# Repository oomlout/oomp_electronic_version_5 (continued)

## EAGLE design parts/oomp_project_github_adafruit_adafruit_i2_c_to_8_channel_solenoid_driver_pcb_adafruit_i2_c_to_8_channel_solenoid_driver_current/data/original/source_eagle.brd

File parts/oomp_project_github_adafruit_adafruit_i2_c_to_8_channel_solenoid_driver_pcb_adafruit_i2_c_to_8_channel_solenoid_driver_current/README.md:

# Project adafruit/Adafruit-I2C-to-8-Channel-Solenoid-Driver-PCB Adafruit I2 C to 8 Channel Solenoid Driver current

[View the project on GitHub](https://github.com/adafruit/Adafruit-I2C-to-8-Channel-Solenoid-Driver-PCB/blob/main/Adafruit%20I2C%20to%208%20Channel%20Solenoid%20Driver.brd)

[Open the interactive board explorer (GitHub Pages)](https://oomlout.github.io/oomp_electronic_version_5/parts/oomp_project_github_adafruit_adafruit_i2_c_to_8_channel_solenoid_driver_pcb_adafruit_i2_c_to_8_channel_solenoid_driver_current/board_explorer.html)

[Browse this project category](../../navigation/oomp/project/github/adafruit/adafruit_i2_c_to_8_channel_solenoid_driver_pcb/adafruit_i2_c_to_8_channel_solenoid_driver/README.md)

Project adafruit/Adafruit-I2C-to-8-Channel-Solenoid-Driver-PCB Adafruit I2 C to 8 Channel Solenoid Driver current is a KiCad project containing 195 extracted component records. The catalogue matcher linked 50 physical placements to OOMP parts.

## Project snapshot

| Item | Count |
| --- | ---: |
| Components | 195 |
| PCB footprints | 135 |
| Mounting and locating holes | 4 |
| Matched OOMP mounting-hole items | 4 |
| Schematic symbols | 137 |
| Matched OOMP components | 50 |
| Unmatched physical components | 72 |
| Front-side placements | 94 |
| Back-side placements | 24 |
| Project version | `current` |
| Git ref | `main` |

## Board

[Original KiCad files](https://github.com/oomlout/oomp_electronic_version_5/tree/main/parts/oomp_project_github_adafruit_adafruit_i2_c_to_8_channel_solenoid_driver_pcb_adafruit_i2_c_to_8_channel_solenoid_driver_current/data/original) · [OOMP KiCad design and local libraries](https://github.com/oomlout/oomp_electronic_version_5/tree/main/parts/oomp_project_github_adafruit_adafruit_i2_c_to_8_channel_solenoid_driver_pcb_adafruit_i2_c_to_8_channel_solenoid_driver_current/data/oomp_design) · [Conversion / skipped-item report](https://github.com/oomlout/oomp_electronic_version_5/blob/main/parts/oomp_project_github_adafruit_adafruit_i2_c_to_8_channel_solenoid_driver_pcb_adafruit_i2_c_to_8_channel_solenoid_driver_current/data/oomp_design/conversion_report.yaml)

The OOMP design is a separate copy. Only symbols and footprints verified against unchanged installed KiCad masters are replaced; custom and modified items are retained.

- Approximate size: **50.8 mm × 27.94 mm**
- Outline source: `KiCad Edge.Cuts`
- Placement drawing: [view `board.svg`](https://github.com/oomlout/oomp_electronic_version_5/blob/main/parts/oomp_project_github_adafruit_adafruit_i2_c_to_8_channel_solenoid_driver_pcb_adafruit_i2_c_to_8_channel_solenoid_driver_current/data/generated_data/src/board.svg)
- PNG placement drawing: [view `board.png`](https://github.com/oomlout/oomp_electronic_version_5/blob/main/parts/oomp_project_github_adafruit_adafruit_i2_c_to_8_channel_solenoid_driver_pcb_adafruit_i2_c_to_8_channel_solenoid_driver_current/data/generated_data/src/board.png)
- 300-pixel placement preview: [view `board_300.png`](https://github.com/oomlout/oomp_electronic_version_5/blob/main/parts/oomp_project_github_adafruit_adafruit_i2_c_to_8_channel_solenoid_driver_pcb_adafruit_i2_c_to_8_channel_solenoid_driver_current/data/generated_data/src/board_300.png)
- Placement drawing with pin names: [view `board_pins.svg`](https://github.com/oomlout/oomp_electronic_version_5/blob/main/parts/oomp_project_github_adafruit_adafruit_i2_c_to_8_channel_solenoid_driver_pcb_adafruit_i2_c_to_8_channel_solenoid_driver_current/data/generated_data/src/board_pins.svg)
- PNG drawing with pin names: [view `board_pins.png`](https://github.com/oomlout/oomp_electronic_version_5/blob/main/parts/oomp_project_github_adafruit_adafruit_i2_c_to_8_channel_solenoid_driver_pcb_adafruit_i2_c_to_8_channel_solenoid_driver_current/data/generated_data/src/board_pins.png)
- 300-pixel pin preview: [view `board_pins_300.png`](https://github.com/oomlout/oomp_electronic_version_5/blob/main/parts/oomp_project_github_adafruit_adafruit_i2_c_to_8_channel_solenoid_driver_pcb_adafruit_i2_c_to_8_channel_solenoid_driver_current/data/generated_data/src/board_pins_300.png)
- Bottom placement drawing: [view `board_bottom.svg`](https://github.com/oomlout/oomp_electronic_version_5/blob/main/parts/oomp_project_github_adafruit_adafruit_i2_c_to_8_channel_solenoid_driver_pcb_adafruit_i2_c_to_8_channel_solenoid_driver_current/data/generated_data/src/board_bottom.svg)
- Bottom PNG placement drawing: [view `board_bottom.png`](https://github.com/oomlout/oomp_electronic_version_5/blob/main/parts/oomp_project_github_adafruit_adafruit_i2_c_to_8_channel_solenoid_driver_pcb_adafruit_i2_c_to_8_channel_solenoid_driver_current/data/generated_data/src/board_bottom.png)
- 300-pixel bottom preview: [view `board_bottom_300.png`](https://github.com/oomlout/oomp_electronic_version_5/blob/main/parts/oomp_project_github_adafruit_adafruit_i2_c_to_8_channel_solenoid_driver_pcb_adafruit_i2_c_to_8_channel_solenoid_driver_current/data/generated_data/src/board_bottom_300.png)
- Bottom placement drawing with pin names: [view `board_pins_bottom.svg`](https://github.com/oomlout/oomp_electronic_version_5/blob/main/parts/oomp_project_github_adafruit_adafruit_i2_c_to_8_channel_solenoid_driver_pcb_adafruit_i2_c_to_8_channel_solenoid_driver_current/data/generated_data/src/board_pins_bottom.svg)
- Bottom PNG drawing with pin names: [view `board_pins_bottom.png`](https://github.com/oomlout/oomp_electronic_version_5/blob/main/parts/oomp_project_github_adafruit_adafruit_i2_c_to_8_channel_solenoid_driver_pcb_adafruit_i2_c_to_8_channel_solenoid_driver_current/data/generated_data/src/board_pins_bottom.png)
- 300-pixel bottom pin preview: [view `board_pins_bottom_300.png`](https://github.com/oomlout/oomp_electronic_version_5/blob/main/parts/oomp_project_github_adafruit_adafruit_i2_c_to_8_channel_solenoid_driver_pcb_adafruit_i2_c_to_8_channel_solenoid_driver_current/data/generated_data/src/board_pins_bottom_300.png)
- Mechanical drawing: [view `board_mechanical.svg`](https://github.com/oomlout/oomp_electronic_version_5/blob/main/parts/oomp_project_github_adafruit_adafruit_i2_c_to_8_channel_solenoid_driver_pcb_adafruit_i2_c_to_8_channel_solenoid_driver_current/data/generated_data/src/board_mechanical.svg)
- Mechanical PNG: [view `board_mechanical.png`](https://github.com/oomlout/oomp_electronic_version_5/blob/main/parts/oomp_project_github_adafruit_adafruit_i2_c_to_8_channel_solenoid_driver_pcb_adafruit_i2_c_to_8_channel_solenoid_driver_current/data/generated_data/src/board_mechanical.png)
- 300-pixel mechanical preview: [view `board_mechanical_300.png`](https://github.com/oomlout/oomp_electronic_version_5/blob/main/parts/oomp_project_github_adafruit_adafruit_i2_c_to_8_channel_solenoid_driver_pcb_adafruit_i2_c_to_8_channel_solenoid_driver_current/data/generated_data/src/board_mechanical_300.png)
- Open the board explorer on GitHub Pages: [explore this board](https://oomlout.github.io/oomp_electronic_version_5/parts/oomp_project_github_adafruit_adafruit_i2_c_to_8_channel_solenoid_driver_pcb_adafruit_i2_c_to_8_channel_solenoid_driver_current/board_explorer.html)
- InteractiveHtmlBom generation is configured; install KiCad or set `KICAD_PYTHON` to its bundled Python to build `data/interactivehtmlbom/ibom.html`.

## Board with pins

## Bottom board with pins

The bottom view is mirrored horizontally so it is shown as viewed from beneath the assembled board.

## Mechanical layer

The table uses a board-relative origin at the minimum X/Y point of `Edge.Cuts`. This point is shown as **0,0** in the mechanical drawing; X increases right and Y increases down. Original KiCad coordinates are retained alongside it.

### Diameter 2.5 mm holes

| OOMP reference | Source | Name | Classification | Role | Board X (mm) | Board Y (mm) | OOMP part |
| --- | --- | --- | --- | --- | ---: | ---: | --- |
| `MH1` | `U$1` | Mounting Hole 2.5 mm Round Plated | `mechanical / mounting_hole / 2_5_mm / round / plated` | mounting | 2.540 | 12.700 | [`mechanical_mounting_hole_2_5_mm_round_plated`](https://github.com/oomlout/oomp_electronic_version_5/tree/main/parts/mechanical_mounting_hole_2_5_mm_round_plated) |
| `MH2` | `U$17` | Mounting Hole 2.5 mm Round Plated | `mechanical / mounting_hole / 2_5_mm / round / plated` | mounting | 48.260 | 12.700 | [`mechanical_mounting_hole_2_5_mm_round_plated`](https://github.com/oomlout/oomp_electronic_version_5/tree/main/parts/mechanical_mounting_hole_2_5_mm_round_plated) |
| `MH3` | `U$19` | Mounting Hole 2.5 mm Round Plated | `mechanical / mounting_hole / 2_5_mm / round / plated` | mounting | 2.540 | 25.400 | [`mechanical_mounting_hole_2_5_mm_round_plated`](https://github.com/oomlout/oomp_electronic_version_5/tree/main/parts/mechanical_mounting_hole_2_5_mm_round_plated) |
| `MH4` | `U$21` | Mounting Hole 2.5 mm Round Plated | `mechanical / mounting_hole / 2_5_mm / round / plated` | mounting | 48.260 | 25.400 | [`mechanical_mounting_hole_2_5_mm_round_plated`](https://github.com/oomlout/oomp_electronic_version_5/tree/main/parts/mechanical_mounting_hole_2_5_mm_round_plated) |

## Bill of materials

| References | Quantity | Description | Value | Footprint | OOMP part |
| --- | ---: | --- | --- | --- | --- |
| C1 | 1 | Capacitor 100 nF 0603 | 0.1uF | `Adafruit I2C to 8 Channel Solenoid Driver-import-fps:0603-NO` | [`electronic_capacitor_0603_100_nano_farad`](https://github.com/oomlout/oomp_electronic_version_5/tree/main/parts/electronic_capacitor_0603_100_nano_farad) |
| C2, C3 | 2 | Capacitor 10 uF 0805 | 10uF | `Adafruit I2C to 8 Channel Solenoid Driver-import-fps:0805-NO` | [`electronic_capacitor_0805_10_micro_farad`](https://github.com/oomlout/oomp_electronic_version_5/tree/main/parts/electronic_capacitor_0805_10_micro_farad) |
| C4 | 1 | 22uF/35V | 22uF/35V | `Adafruit I2C to 8 Channel Solenoid Driver-import-fps:PANASONIC_C` | unmatched |
| CONN3, CONN4 | 2 | Connector JST Sh SM04B-SRSS-TB | STEMMA_I2C_QT | `Adafruit I2C to 8 Channel Solenoid Driver-import-fps:JST_SH4` | [`electronic_connector_jst_sh_1_mm_pitch_surface_mount_right_angle_4_pin_jst_sm04b_srss_tb`](https://github.com/oomlout/oomp_electronic_version_5/tree/main/parts/electronic_connector_jst_sh_1_mm_pitch_surface_mount_right_angle_4_pin_jst_sm04b_srss_tb) |
| D1 | 1 | LED Green 0603 | GREEN | `Adafruit I2C to 8 Channel Solenoid Driver-import-fps:CHIPLED_0603_NOOUTLINE` | [`electronic_led_0603_green`](https://github.com/oomlout/oomp_electronic_version_5/tree/main/parts/electronic_led_0603_green) |
| D2, D3, D4, D5, D6, D7, D8, D9 | 8 | Diode 1N4148WS SOD-323 | 1N4148 | `Adafruit I2C to 8 Channel Solenoid Driver-import-fps:SOD-323` | [`electronic_diode_switching_sod_323_onsemi_1n4148ws`](https://github.com/oomlout/oomp_electronic_version_5/tree/main/parts/electronic_diode_switching_sod_323_onsemi_1n4148ws) |
| D10, D11, D12, D13, D14, D15, D16, D17 | 8 | LED Red 0603 | RED | `Adafruit I2C to 8 Channel Solenoid Driver-import-fps:CHIPLED_0603_NOOUTLINE` | [`electronic_led_0603_red`](https://github.com/oomlout/oomp_electronic_version_5/tree/main/parts/electronic_led_0603_red) |
| IC1 | 1 | MCP23017ML | MCP23017ML | `Adafruit I2C to 8 Channel Solenoid Driver-import-fps:QFN28-ML_6X6MM` | unmatched |
| JP2, JP8 | 2 | Connector Header PZ254V-12-8P | 8p 2.54mm Terminal | `Adafruit I2C to 8 Channel Solenoid Driver-import-fps:1X08_2.54MMTERMINAL` | [`electronic_connector_header_2_54_mm_pitch_through_hole_8_pin`](https://github.com/oomlout/oomp_electronic_version_5/tree/main/parts/electronic_connector_header_2_54_mm_pitch_through_hole_8_pin) |
| JP3, JP4 | 2 | Connector Header PZ2.54-S04P-A60 |  | `Adafruit I2C to 8 Channel Solenoid Driver-import-fps:1X04_ROUND` | [`electronic_connector_header_2_54_mm_pitch_through_hole_4_pin`](https://github.com/oomlout/oomp_electronic_version_5/tree/main/parts/electronic_connector_header_2_54_mm_pitch_through_hole_4_pin) |
| JP6, JP7 | 2 | Connector Header PZ254V-12-8P |  | `Adafruit I2C to 8 Channel Solenoid Driver-import-fps:1X08_ROUND_70` | [`electronic_connector_header_2_54_mm_pitch_through_hole_8_pin`](https://github.com/oomlout/oomp_electronic_version_5/tree/main/parts/electronic_connector_header_2_54_mm_pitch_through_hole_8_pin) |
| PLABEL0 | 1 | Adafruit I2C to 8 Channel Solenoid Driver-import-fps:PLABEL0 |  | `Adafruit I2C to 8 Channel Solenoid Driver-import-fps:PLABEL0` | unmatched |
| PLABEL1 | 1 | Adafruit I2C to 8 Channel Solenoid Driver-import-fps:PLABEL1 |  | `Adafruit I2C to 8 Channel Solenoid Driver-import-fps:PLABEL1` | unmatched |
| PLABEL2 | 1 | Adafruit I2C to 8 Channel Solenoid Driver-import-fps:PLABEL2 |  | `Adafruit I2C to 8 Channel Solenoid Driver-import-fps:PLABEL2` | unmatched |
| PLABEL3 | 1 | Adafruit I2C to 8 Channel Solenoid Driver-import-fps:PLABEL3 |  | `Adafruit I2C to 8 Channel Solenoid Driver-import-fps:PLABEL3` | unmatched |
| PLABEL4 | 1 | Adafruit I2C to 8 Channel Solenoid Driver-import-fps:PLABEL4 |  | `Adafruit I2C to 8 Channel Solenoid Driver-import-fps:PLABEL4` | unmatched |
| PLABEL5 | 1 | Adafruit I2C to 8 Channel Solenoid Driver-import-fps:PLABEL5 |  | `Adafruit I2C to 8 Channel Solenoid Driver-import-fps:PLABEL5` | unmatched |
| PLABEL6 | 1 | Adafruit I2C to 8 Channel Solenoid Driver-import-fps:PLABEL6 |  | `Adafruit I2C to 8 Channel Solenoid Driver-import-fps:PLABEL6` | unmatched |
| PLABEL7 | 1 | Adafruit I2C to 8 Channel Solenoid Driver-import-fps:PLABEL7 |  | `Adafruit I2C to 8 Channel Solenoid Driver-import-fps:PLABEL7` | unmatched |
| PLABEL8 | 1 | Adafruit I2C to 8 Channel Solenoid Driver-import-fps:PLABEL8 |  | `Adafruit I2C to 8 Channel Solenoid Driver-import-fps:PLABEL8` | unmatched |
| PLABEL9 | 1 | Adafruit I2C to 8 Channel Solenoid Driver-import-fps:PLABEL9 |  | `Adafruit I2C to 8 Channel Solenoid Driver-import-fps:PLABEL9` | unmatched |
| PLABEL10 | 1 | Adafruit I2C to 8 Channel Solenoid Driver-import-fps:PLABEL10 |  | `Adafruit I2C to 8 Channel Solenoid Driver-import-fps:PLABEL10` | unmatched |
| PLABEL11 | 1 | Adafruit I2C to 8 Channel Solenoid Driver-import-fps:PLABEL11 |  | `Adafruit I2C to 8 Channel Solenoid Driver-import-fps:PLABEL11` | unmatched |
| PLABEL12 | 1 | Adafruit I2C to 8 Channel Solenoid Driver-import-fps:PLABEL12 |  | `Adafruit I2C to 8 Channel Solenoid Driver-import-fps:PLABEL12` | unmatched |
| PLABEL13 | 1 | Adafruit I2C to 8 Channel Solenoid Driver-import-fps:PLABEL13 |  | `Adafruit I2C to 8 Channel Solenoid Driver-import-fps:PLABEL13` | unmatched |
| PLABEL14 | 1 | Adafruit I2C to 8 Channel Solenoid Driver-import-fps:PLABEL14 |  | `Adafruit I2C to 8 Channel Solenoid Driver-import-fps:PLABEL14` | unmatched |
| PLABEL15 | 1 | Adafruit I2C to 8 Channel Solenoid Driver-import-fps:PLABEL15 |  | `Adafruit I2C to 8 Channel Solenoid Driver-import-fps:PLABEL15` | unmatched |
| PLABEL16 | 1 | Adafruit I2C to 8 Channel Solenoid Driver-import-fps:PLABEL16 |  | `Adafruit I2C to 8 Channel Solenoid Driver-import-fps:PLABEL16` | unmatched |
| PLABEL17 | 1 | Adafruit I2C to 8 Channel Solenoid Driver-import-fps:PLABEL17 |  | `Adafruit I2C to 8 Channel Solenoid Driver-import-fps:PLABEL17` | unmatched |
| PLABEL18 | 1 | Adafruit I2C to 8 Channel Solenoid Driver-import-fps:PLABEL18 |  | `Adafruit I2C to 8 Channel Solenoid Driver-import-fps:PLABEL18` | unmatched |
| PLABEL19 | 1 | Adafruit I2C to 8 Channel Solenoid Driver-import-fps:PLABEL19 |  | `Adafruit I2C to 8 Channel Solenoid Driver-import-fps:PLABEL19` | unmatched |
| PLABEL20 | 1 | Adafruit I2C to 8 Channel Solenoid Driver-import-fps:PLABEL20 |  | `Adafruit I2C to 8 Channel Solenoid Driver-import-fps:PLABEL20` | unmatched |
| PLABEL21 | 1 | Adafruit I2C to 8 Channel Solenoid Driver-import-fps:PLABEL21 |  | `Adafruit I2C to 8 Channel Solenoid Driver-import-fps:PLABEL21` | unmatched |
| PLABEL22 | 1 | Adafruit I2C to 8 Channel Solenoid Driver-import-fps:PLABEL22 |  | `Adafruit I2C to 8 Channel Solenoid Driver-import-fps:PLABEL22` | unmatched |
| PLABEL23 | 1 | Adafruit I2C to 8 Channel Solenoid Driver-import-fps:PLABEL23 |  | `Adafruit I2C to 8 Channel Solenoid Driver-import-fps:PLABEL23` | unmatched |
| PLABEL24 | 1 | Adafruit I2C to 8 Channel Solenoid Driver-import-fps:PLABEL24 |  | `Adafruit I2C to 8 Channel Solenoid Driver-import-fps:PLABEL24` | unmatched |
| PLABEL25 | 1 | Adafruit I2C to 8 Channel Solenoid Driver-import-fps:PLABEL25 |  | `Adafruit I2C to 8 Channel Solenoid Driver-import-fps:PLABEL25` | unmatched |
| PLABEL26 | 1 | Adafruit I2C to 8 Channel Solenoid Driver-import-fps:PLABEL26 |  | `Adafruit I2C to 8 Channel Solenoid Driver-import-fps:PLABEL26` | unmatched |
| PLABEL27 | 1 | Adafruit I2C to 8 Channel Solenoid Driver-import-fps:PLABEL27 |  | `Adafruit I2C to 8 Channel Solenoid Driver-import-fps:PLABEL27` | unmatched |
| PLABEL28 | 1 | Adafruit I2C to 8 Channel Solenoid Driver-import-fps:PLABEL28 |  | `Adafruit I2C to 8 Channel Solenoid Driver-import-fps:PLABEL28` | unmatched |
| PLABEL29 | 1 | Adafruit I2C to 8 Channel Solenoid Driver-import-fps:PLABEL29 |  | `Adafruit I2C to 8 Channel Solenoid Driver-import-fps:PLABEL29` | unmatched |
| PLABEL30 | 1 | Adafruit I2C to 8 Channel Solenoid Driver-import-fps:PLABEL30 |  | `Adafruit I2C to 8 Channel Solenoid Driver-import-fps:PLABEL30` | unmatched |
| PLABEL31 | 1 | Adafruit I2C to 8 Channel Solenoid Driver-import-fps:PLABEL31 |  | `Adafruit I2C to 8 Channel Solenoid Driver-import-fps:PLABEL31` | unmatched |
| PLABEL32 | 1 | Adafruit I2C to 8 Channel Solenoid Driver-import-fps:PLABEL32 |  | `Adafruit I2C to 8 Channel Solenoid Driver-import-fps:PLABEL32` | unmatched |
| PLABEL33 | 1 | Adafruit I2C to 8 Channel Solenoid Driver-import-fps:PLABEL33 |  | `Adafruit I2C to 8 Channel Solenoid Driver-import-fps:PLABEL33` | unmatched |
| PLABEL34 | 1 | Adafruit I2C to 8 Channel Solenoid Driver-import-fps:PLABEL34 |  | `Adafruit I2C to 8 Channel Solenoid Driver-import-fps:PLABEL34` | unmatched |
| PLABEL35 | 1 | Adafruit I2C to 8 Channel Solenoid Driver-import-fps:PLABEL35 |  | `Adafruit I2C to 8 Channel Solenoid Driver-import-fps:PLABEL35` | unmatched |
| PLABEL36 | 1 | Adafruit I2C to 8 Channel Solenoid Driver-import-fps:PLABEL36 |  | `Adafruit I2C to 8 Channel Solenoid Driver-import-fps:PLABEL36` | unmatched |
| PLABEL37 | 1 | Adafruit I2C to 8 Channel Solenoid Driver-import-fps:PLABEL37 |  | `Adafruit I2C to 8 Channel Solenoid Driver-import-fps:PLABEL37` | unmatched |
| PLABEL38 | 1 | Adafruit I2C to 8 Channel Solenoid Driver-import-fps:PLABEL38 |  | `Adafruit I2C to 8 Channel Solenoid Driver-import-fps:PLABEL38` | unmatched |
| PLABEL39 | 1 | Adafruit I2C to 8 Channel Solenoid Driver-import-fps:PLABEL39 |  | `Adafruit I2C to 8 Channel Solenoid Driver-import-fps:PLABEL39` | unmatched |
| PLABEL40 | 1 | Adafruit I2C to 8 Channel Solenoid Driver-import-fps:PLABEL40 |  | `Adafruit I2C to 8 Channel Solenoid Driver-import-fps:PLABEL40` | unmatched |
| PLABEL41 | 1 | Adafruit I2C to 8 Channel Solenoid Driver-import-fps:PLABEL41 |  | `Adafruit I2C to 8 Channel Solenoid Driver-import-fps:PLABEL41` | unmatched |
| PLABEL42 | 1 | Adafruit I2C to 8 Channel Solenoid Driver-import-fps:PLABEL42 |  | `Adafruit I2C to 8 Channel Solenoid Driver-import-fps:PLABEL42` | unmatched |
| PLABEL43 | 1 | Adafruit I2C to 8 Channel Solenoid Driver-import-fps:PLABEL43 |  | `Adafruit I2C to 8 Channel Solenoid Driver-import-fps:PLABEL43` | unmatched |
| PLABEL44 | 1 | Adafruit I2C to 8 Channel Solenoid Driver-import-fps:PLABEL44 |  | `Adafruit I2C to 8 Channel Solenoid Driver-import-fps:PLABEL44` | unmatched |
| PLABEL45 | 1 | Adafruit I2C to 8 Channel Solenoid Driver-import-fps:PLABEL45 |  | `Adafruit I2C to 8 Channel Solenoid Driver-import-fps:PLABEL45` | unmatched |
| PLABEL46 | 1 | Adafruit I2C to 8 Channel Solenoid Driver-import-fps:PLABEL46 |  | `Adafruit I2C to 8 Channel Solenoid Driver-import-fps:PLABEL46` | unmatched |
| PLABEL47 | 1 | Adafruit I2C to 8 Channel Solenoid Driver-import-fps:PLABEL47 |  | `Adafruit I2C to 8 Channel Solenoid Driver-import-fps:PLABEL47` | unmatched |
| PLABEL48 | 1 | Adafruit I2C to 8 Channel Solenoid Driver-import-fps:PLABEL48 |  | `Adafruit I2C to 8 Channel Solenoid Driver-import-fps:PLABEL48` | unmatched |
| PLABEL49 | 1 | Adafruit I2C to 8 Channel Solenoid Driver-import-fps:PLABEL49 |  | `Adafruit I2C to 8 Channel Solenoid Driver-import-fps:PLABEL49` | unmatched |
| PLABEL50 | 1 | Adafruit I2C to 8 Channel Solenoid Driver-import-fps:PLABEL50 |  | `Adafruit I2C to 8 Channel Solenoid Driver-import-fps:PLABEL50` | unmatched |
| PLABEL51 | 1 | Adafruit I2C to 8 Channel Solenoid Driver-import-fps:PLABEL51 |  | `Adafruit I2C to 8 Channel Solenoid Driver-import-fps:PLABEL51` | unmatched |
| PLABEL52 | 1 | Adafruit I2C to 8 Channel Solenoid Driver-import-fps:PLABEL52 |  | `Adafruit I2C to 8 Channel Solenoid Driver-import-fps:PLABEL52` | unmatched |
| PLABEL53 | 1 | Adafruit I2C to 8 Channel Solenoid Driver-import-fps:PLABEL53 |  | `Adafruit I2C to 8 Channel Solenoid Driver-import-fps:PLABEL53` | unmatched |
| PLABEL54 | 1 | Adafruit I2C to 8 Channel Solenoid Driver-import-fps:PLABEL54 |  | `Adafruit I2C to 8 Channel Solenoid Driver-import-fps:PLABEL54` | unmatched |
| PLABEL55 | 1 | Adafruit I2C to 8 Channel Solenoid Driver-import-fps:PLABEL55 |  | `Adafruit I2C to 8 Channel Solenoid Driver-import-fps:PLABEL55` | unmatched |
| PLABEL56 | 1 | Adafruit I2C to 8 Channel Solenoid Driver-import-fps:PLABEL56 |  | `Adafruit I2C to 8 Channel Solenoid Driver-import-fps:PLABEL56` | unmatched |
| PLABEL57 | 1 | Adafruit I2C to 8 Channel Solenoid Driver-import-fps:PLABEL57 |  | `Adafruit I2C to 8 Channel Solenoid Driver-import-fps:PLABEL57` | unmatched |
| PLABEL58 | 1 | Adafruit I2C to 8 Channel Solenoid Driver-import-fps:PLABEL58 |  | `Adafruit I2C to 8 Channel Solenoid Driver-import-fps:PLABEL58` | unmatched |
| PLABEL59 | 1 | Adafruit I2C to 8 Channel Solenoid Driver-import-fps:PLABEL59 |  | `Adafruit I2C to 8 Channel Solenoid Driver-import-fps:PLABEL59` | unmatched |
| PLABEL60 | 1 | Adafruit I2C to 8 Channel Solenoid Driver-import-fps:PLABEL60 |  | `Adafruit I2C to 8 Channel Solenoid Driver-import-fps:PLABEL60` | unmatched |
| Q1, Q2, Q3, Q4, Q5, Q6, Q7, Q8 | 8 | AO3406 | AO3406 | `Adafruit I2C to 8 Channel Solenoid Driver-import-fps:SOT23-WIDE` | unmatched |
| R1, R3 | 2 | Resistor 10000 Ohm 0603 | 10K Pack | `Adafruit I2C to 8 Channel Solenoid Driver-import-fps:RESPACK_4X0603` | [`electronic_resistor_0603_10000_ohm`](https://github.com/oomlout/oomp_electronic_version_5/tree/main/parts/electronic_resistor_0603_10000_ohm) |
| R2, R4, R5, R6, R7, R8, R9, R10, R11, R12, R13, R14, R15, R16, R17, R18 | 16 | Resistor 10000 Ohm 0603 | 10K | `Adafruit I2C to 8 Channel Solenoid Driver-import-fps:0603-NO` | [`electronic_resistor_0603_10000_ohm`](https://github.com/oomlout/oomp_electronic_version_5/tree/main/parts/electronic_resistor_0603_10000_ohm) |
| X1 | 1 | 2p 3.5mm Terminal | 2p 3.5mm Terminal | `Adafruit I2C to 8 Channel Solenoid Driver-import-fps:TERMBLOCK_1X2-3.5MM` | unmatched |

## Main nets

| Net | Pads | Components |
| --- | ---: | --- |
| `GND` | 42 | C1, C2, C3, C4, CONN3, CONN4, IC1, JP3, JP7, Q1, Q2, Q3, Q4, Q5, Q6, Q7, Q8, R1, R3, R4, R5, R6, R7, R8, R9, R10, R11, SJ1, X1 |
| `V+` | 26 | C4, D2, D3, D4, D5, D6, D7, D8, D9, D14, D15, D16, D17, JP2, JP8, R2, R12, R13, R14, X1 |
| `VCC` | 15 | ADDR0, ADDR1, ADDR2, C1, C2, C3, CONN3, CONN4, IC1, JP3, R1, R3 |
| `SCL` | 5 | CONN3, CONN4, IC1, JP3, R3 |
| `SDA` | 5 | CONN3, CONN4, IC1, JP3, R3 |
| `A0` | 4 | ADDR0, IC1, JP4, R3 |
| `A1` | 4 | ADDR1, IC1, JP4, R3 |
| `A2` | 4 | ADDR2, IC1, JP4, R1 |
| `OUT0` | 4 | D5, D10, JP2, Q4 |
| `OUT1` | 4 | D4, D11, JP2, Q3 |
| `OUT2` | 4 | D2, D12, JP2, Q2 |
| `OUT3` | 4 | D3, D13, JP2, Q1 |
| `OUT4` | 4 | D9, JP8, Q8, R15 |
| `OUT5` | 4 | D8, JP8, Q7, R16 |
| `OUT6` | 4 | D7, JP8, Q6, R17 |
| `OUT7` | 4 | D6, JP8, Q5, R18 |
| `GPA0` | 3 | IC1, Q4, R7 |
| `GPA1` | 3 | IC1, Q3, R6 |
| `GPA2` | 3 | IC1, Q2, R5 |
| `GPA3` | 3 | IC1, Q1, R4 |

## Design notes

- The extracted board outline is approximately 50.8 mm by 27.94 mm.
- Placement data contains 94 front-side and 24 back-side components.

## Review notes

- 72 physical component records are not yet matched to an OOMP part.

- Part identities needing a manufacturer/LCSC decision: [`lcsc_review.yaml`](https://github.com/oomlout/oomp_electronic_version_5/blob/main/parts/oomp_project_github_adafruit_adafruit_i2_c_to_8_channel_solenoid_driver_pcb_adafruit_i2_c_to_8_channel_solenoid_driver_current/data/generated_data/lcsc_review.yaml)
- Browser-only research and datasheet queue: [`browser_research_queue.md`](https://github.com/oomlout/oomp_electronic_version_5/blob/main/parts/oomp_project_github_adafruit_adafruit_i2_c_to_8_channel_solenoid_driver_pcb_adafruit_i2_c_to_8_channel_solenoid_driver_current/data/generated_data/browser_research_queue.md)

## Generated source bundle

- Project image assets: [`data/generated_data/src`](https://github.com/oomlout/oomp_electronic_version_5/tree/main/parts/oomp_project_github_adafruit_adafruit_i2_c_to_8_channel_solenoid_driver_pcb_adafruit_i2_c_to_8_channel_solenoid_driver_current/data/generated_data/src)
- Copied component source manifest: `data/project_source/manifest.yaml` (generated locally and ignored by Git)
- Matched OOMP source parts copied: 10

## Source files

- Schematic: `data/kicad_file.kicad_sch`
- PCB: `data/kicad_file.kicad_pcb`

---

Generated deterministically by `kicad_agents.project_summary_agent`; no LLM-authored content is used.

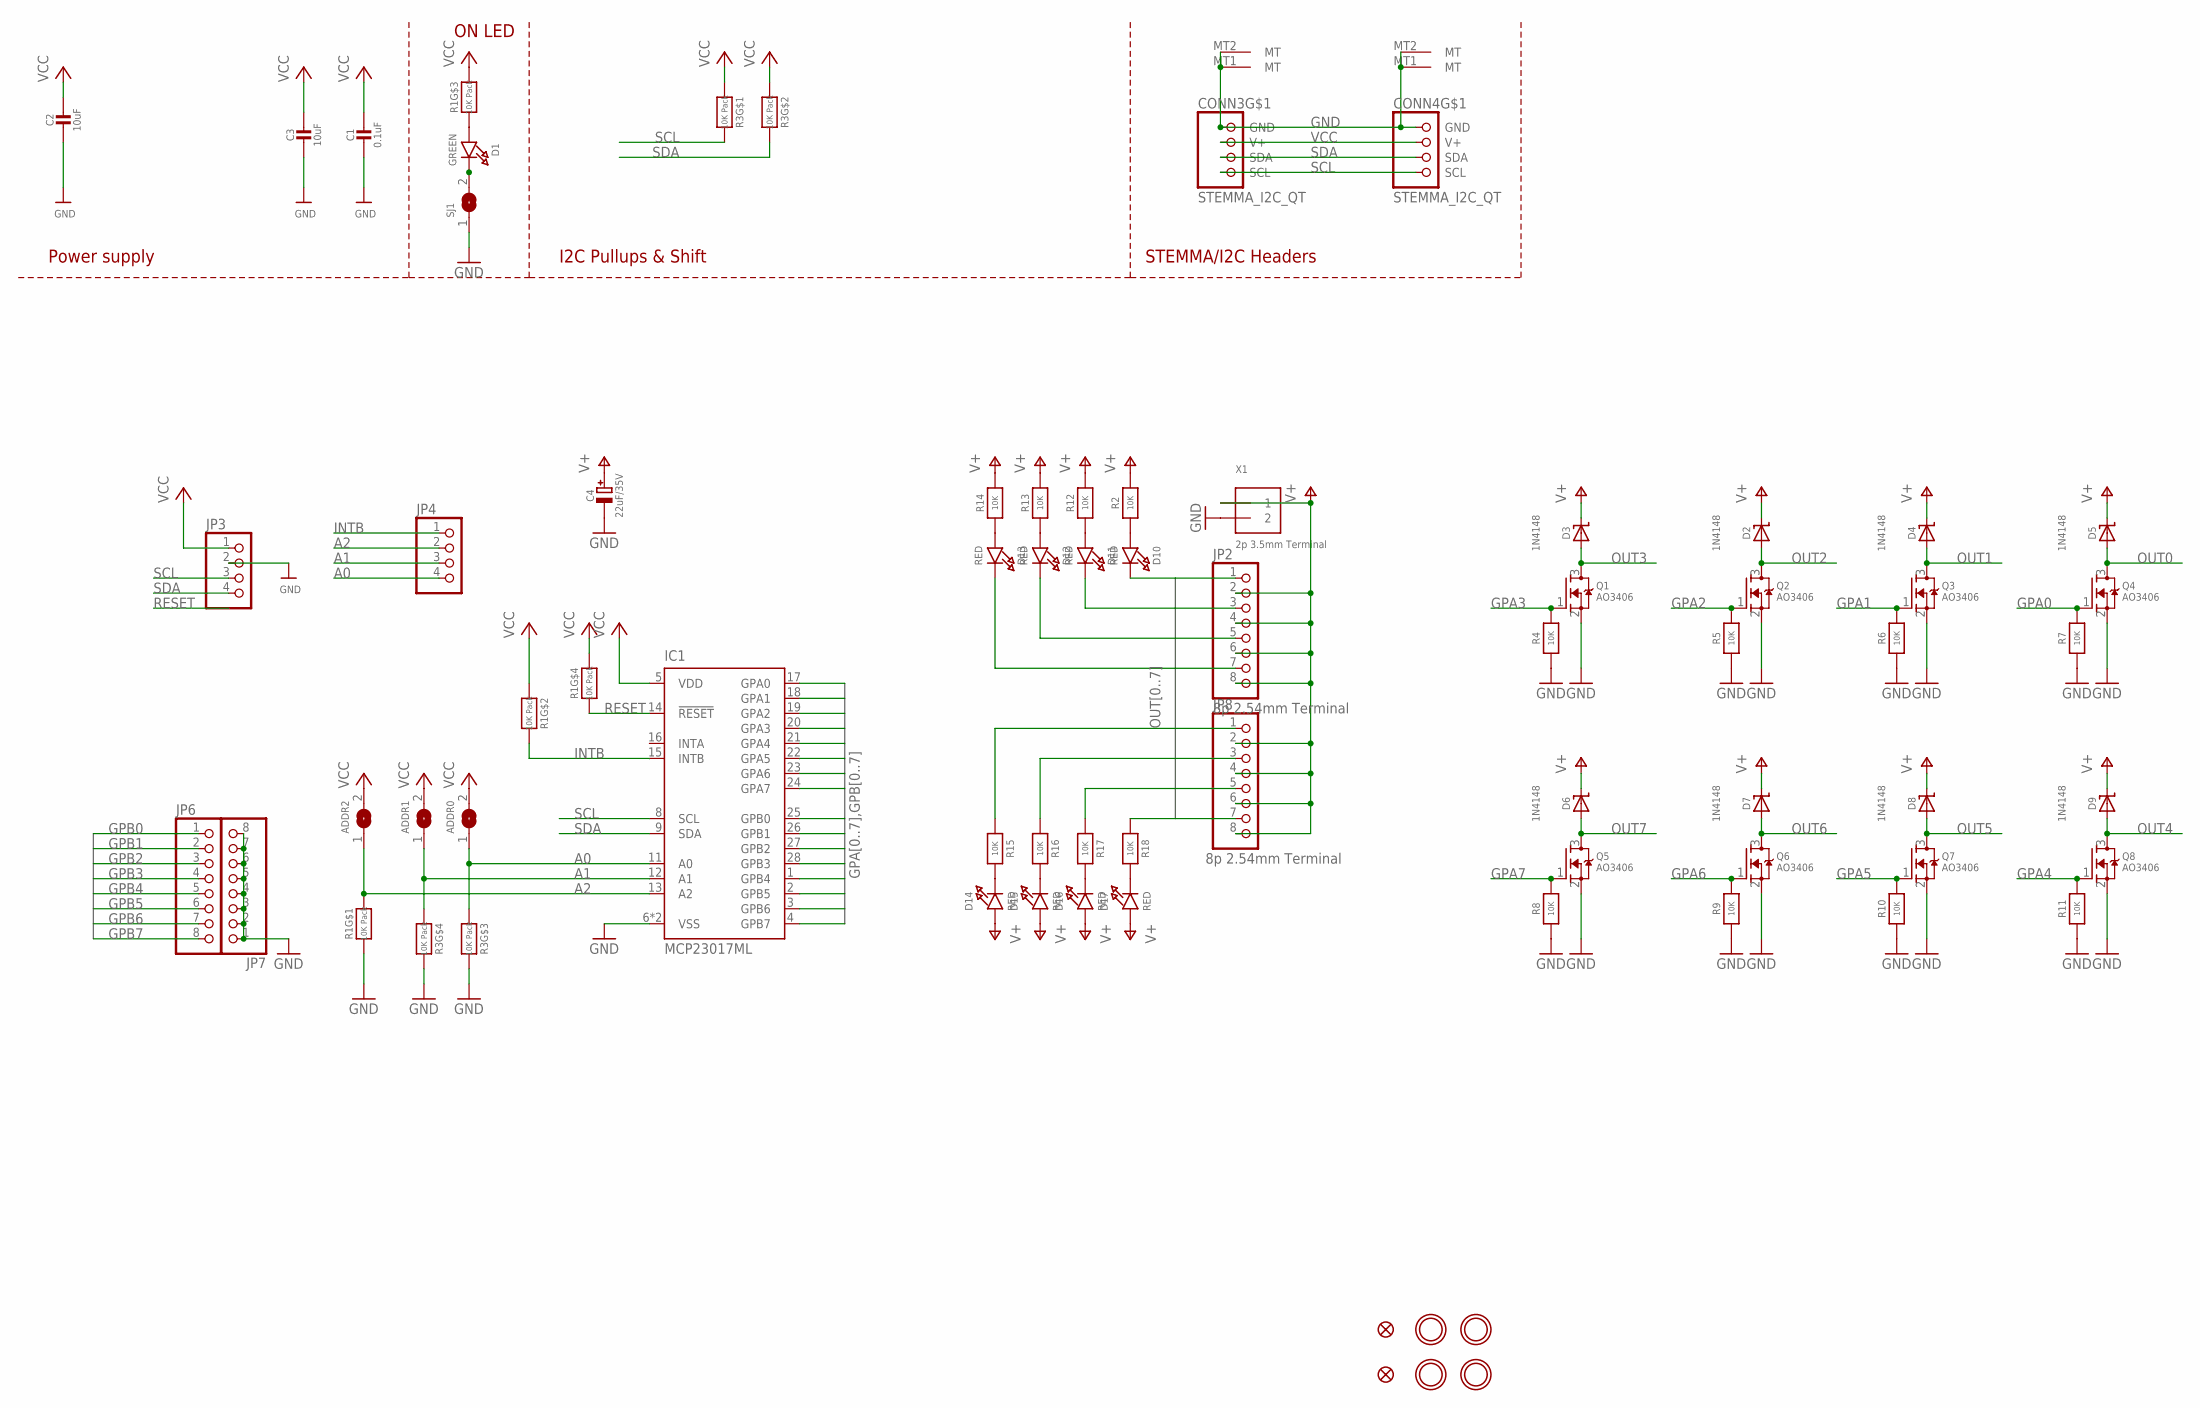
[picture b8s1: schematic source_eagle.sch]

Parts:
ADDR0, ADDR1, ADDR2: SOLDERJUMPER; SOLDERJUMPER_ARROW_NOPASTE
C1: 0.1uF; 0603-NO
C2, C3: 10uF; 0805-NO
C4: 22uF/35V; PANASONIC_C
CONN3, CONN4: STEMMA_I2C_QT; JST_SH4
D1: GREEN; CHIPLED_0603_NOOUTLINE
D2, D3, D4, D5, D6, D7, D8, D9: 1N4148; SOD-323
D10, D11, D12, D13, D14, D15, D16, D17: RED; CHIPLED_0603_NOOUTLINE
FID3, FID4: FIDUCIAL_1MM
IC1: MCP23017ML; QFN28-ML_6X6MM
JP2, JP8: 8p 2.54mm Terminal; 1X08_2.54MMTERMINAL
JP3, JP4: HEADER-1X4ROUND; 1X04_ROUND
JP6, JP7: HEADER-1X870MIL; 1X08_ROUND_70
Q1, Q2, Q3, Q4, Q5, Q6, Q7, Q8: AO3406; SOT23-WIDE
R1, R3: 10K Pack; RESPACK_4X0603
R2, R4, R5, R6, R7, R8, R9, R10, R11, R12, R13, R14, R15, R16, R17, R18: 10K; 0603-NO
SJ1: SOLDERJUMPERCLOSED; SOLDERJUMPER_CLOSEDWIRE
U$1, U$17, U$19, U$21: MOUNTINGHOLE2.5; MOUNTINGHOLE_2.5_PLATED
X1: 2p 3.5mm Terminal; TERMBLOCK_1X2-3.5MM

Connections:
A0: ADDR0.1, IC1.11 (A0), JP4.4, R3.3 (1)
A1: ADDR1.1, IC1.12 (A1), JP4.3, R3.4 (1)
A2: ADDR2.1, IC1.13 (A2), JP4.2, R1.8 (2)
GND: C1.2, C2.2, C3.2, C4.-, CONN3.1 (GND), CONN3.MT1 (MT), CONN3.MT2 (MT), CONN4.1 (GND), CONN4.MT1 (MT), CONN4.MT2 (MT), IC1.6 (VSS), IC1.EXP (VSS), JP3.2, JP7.1, JP7.2, JP7.3, JP7.4, JP7.5, JP7.6, JP7.7, JP7.8, Q1.2 (S), Q2.2 (S), Q3.2 (S), Q4.2 (S), Q5.2 (S), Q6.2 (S), Q7.2 (S), Q8.2 (S), R1.1, R3.5 (2), R3.6 (2), R4.1, R5.1, R6.1, R7.1, R8.1, R9.1, R10.1, R11.1, SJ1.1, X1.2
GPA0: IC1.17 (GPA0), Q4.1 (G), R7.2
GPA1: IC1.18 (GPA1), Q3.1 (G), R6.2
GPA2: IC1.19 (GPA2), Q2.1 (G), R5.2
GPA3: IC1.20 (GPA3), Q1.1 (G), R4.2
GPA4: IC1.21 (GPA4), Q8.1 (G), R11.2
GPA5: IC1.22 (GPA5), Q7.1 (G), R10.2
GPA6: IC1.23 (GPA6), Q6.1 (G), R9.2
GPA7: IC1.24 (GPA7), Q5.1 (G), R8.2
GPB0: IC1.25 (GPB0), JP6.1
GPB1: IC1.26 (GPB1), JP6.2
GPB2: IC1.27 (GPB2), JP6.3
GPB3: IC1.28 (GPB3), JP6.4
GPB4: IC1.1 (GPB4), JP6.5
GPB5: IC1.2 (GPB5), JP6.6
GPB6: IC1.3 (GPB6), JP6.7
GPB7: IC1.4 (GPB7), JP6.8
INTB: IC1.15 (INTB), JP4.1, R1.7 (2)
unnamed: D1.A, R1.3 (1)
unnamed: D1.C, SJ1.2
unnamed: D10.A, R2.1
unnamed: D11.A, R12.1
unnamed: D12.A, R13.1
unnamed: D13.A, R14.1
unnamed: D14.C, R15.2
unnamed: D15.C, R16.2
unnamed: D16.C, R17.2
unnamed: D17.C, R18.2
OUT0: D5.A, D10.C, JP2.1, Q4.3 (D)
OUT1: D4.A, D11.C, JP2.3, Q3.3 (D)
OUT2: D2.A, D12.C, JP2.5, Q2.3 (D)
OUT3: D3.A, D13.C, JP2.7, Q1.3 (D)
OUT4: D9.A, JP8.1, Q8.3 (D), R15.1
OUT5: D8.A, JP8.3, Q7.3 (D), R16.1
OUT6: D7.A, JP8.5, Q6.3 (D), R17.1
OUT7: D6.A, JP8.7, Q5.3 (D), R18.1
RESET: IC1.14 (!RESET), R1.4 (1)
SCL: CONN3.4 (SCL), CONN4.4 (SCL), IC1.8 (SCL), JP3.3, R3.8 (2)
SDA: CONN3.3 (SDA), CONN4.3 (SDA), IC1.9 (SDA), JP3.4, R3.7 (2)
V+: C4.+, D2.C, D3.C, D4.C, D5.C, D6.C, D7.C, D8.C, D9.C, D14.A, D15.A, D16.A, D17.A, JP2.2, JP2.4, JP2.6, JP2.8, JP8.2, JP8.4, JP8.6, JP8.8, R2.2, R12.2, R13.2, R14.2, X1.1
VCC: ADDR0.2, ADDR1.2, ADDR2.2, C1.1, C2.1, C3.1, CONN3.2 (V+), CONN4.2 (V+), IC1.5 (VDD), JP3.1, R1.2 (1), R1.5 (2), R1.6 (2), R3.1, R3.2 (1)

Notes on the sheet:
I2C Pullups & Shift
STEMMA/I2C Headers
ON LED
Power supply

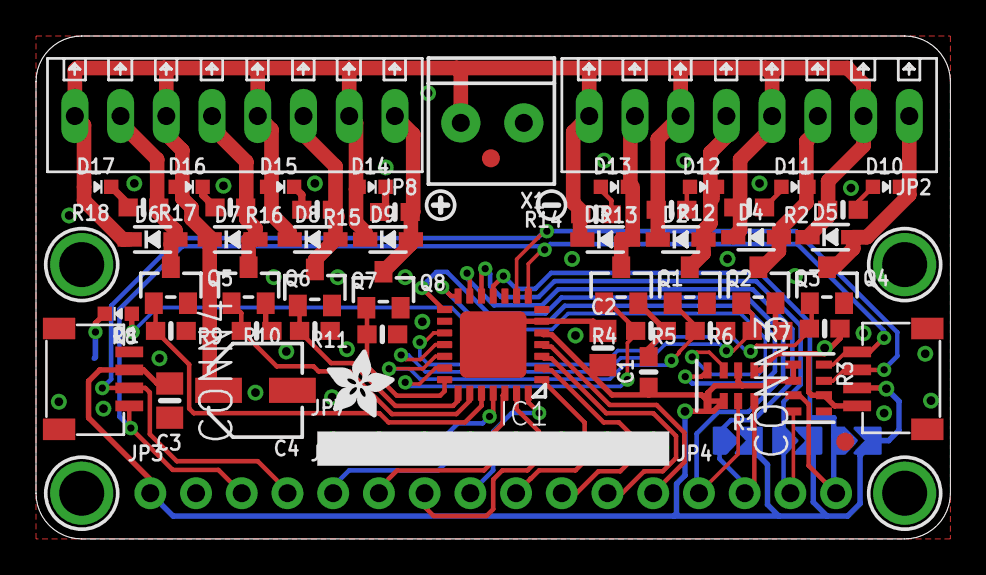
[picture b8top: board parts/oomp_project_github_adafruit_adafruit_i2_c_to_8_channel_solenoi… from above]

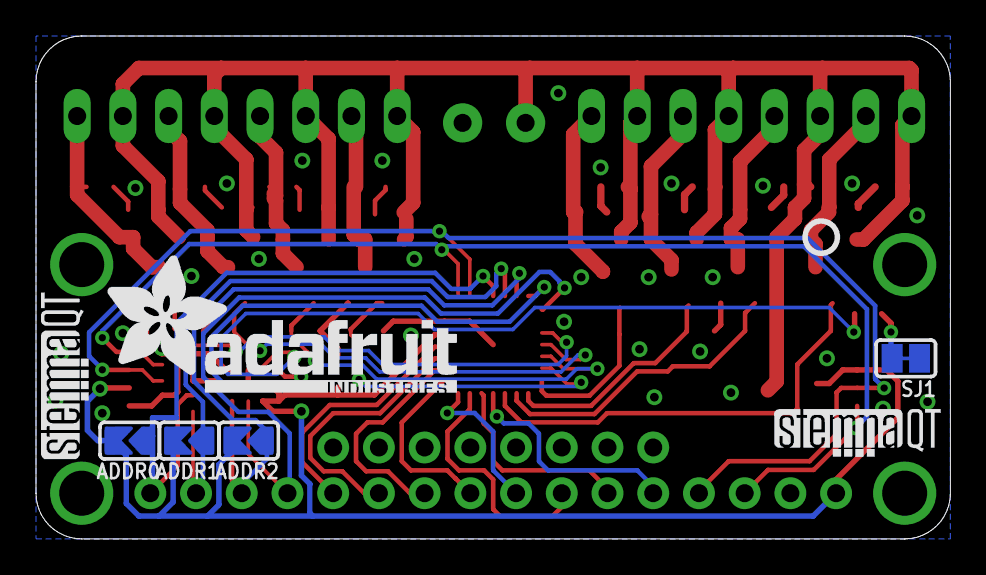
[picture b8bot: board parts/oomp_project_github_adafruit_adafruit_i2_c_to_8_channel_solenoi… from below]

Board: 2 copper layers, 50.8 x 27.9 mm, 135 parts (32 on the bottom side), 44 nets.

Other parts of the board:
PLABEL0: PLABEL0
PLABEL1: PLABEL1
PLABEL2: PLABEL2
PLABEL3: PLABEL3
PLABEL4: PLABEL4
PLABEL5: PLABEL5
PLABEL6: PLABEL6
PLABEL7: PLABEL7
PLABEL8: PLABEL8
PLABEL9: PLABEL9
PLABEL10: PLABEL10
PLABEL11: PLABEL11
PLABEL12: PLABEL12
PLABEL13: PLABEL13
PLABEL14: PLABEL14
PLABEL15: PLABEL15
PLABEL16: PLABEL16
PLABEL17: PLABEL17
PLABEL18: PLABEL18
PLABEL19: PLABEL19
PLABEL20: PLABEL20
PLABEL21: PLABEL21
PLABEL22: PLABEL22
PLABEL23: PLABEL23
PLABEL24: PLABEL24
PLABEL25: PLABEL25
PLABEL26: PLABEL26
PLABEL27: PLABEL27
PLABEL28: PLABEL28
PLABEL29: PLABEL29
PLABEL30: PLABEL30
PLABEL31: PLABEL31
PLABEL32: PLABEL32
PLABEL33: PLABEL33
PLABEL34: PLABEL34
PLABEL35: PLABEL35
PLABEL36: PLABEL36
PLABEL37: PLABEL37
PLABEL38: PLABEL38
PLABEL39: PLABEL39
PLABEL40: PLABEL40
PLABEL41: PLABEL41
PLABEL42: PLABEL42
PLABEL43: PLABEL43
PLABEL44: PLABEL44
PLABEL45: PLABEL45
PLABEL46: PLABEL46
PLABEL47: PLABEL47
PLABEL48: PLABEL48
PLABEL49: PLABEL49
PLABEL50: PLABEL50
PLABEL51: PLABEL51
PLABEL52: PLABEL52
PLABEL53: PLABEL53
PLABEL54: PLABEL54
PLABEL55: PLABEL55
PLABEL56: PLABEL56
PLABEL57: PLABEL57
PLABEL58: PLABEL58
PLABEL59: PLABEL59
PLABEL60: PLABEL60
U$2: PLUS; SYMBOL_PLUS
U$3: SYMBOL_MINUS
U$4: ADAFRUIT_3.5MM
U$7: ADAFRUIT_TEXT_20MM
U$25: PCBFEAT-REV-040
U$30, U$31: STEMMAQT
